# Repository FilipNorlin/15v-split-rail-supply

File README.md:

\Delta I_{L} = 0# Design and Scaling of a ±17 V 4 A DC-DC Converter with LM3478

## LM3478 Useful Design Formulas

---

### 1. Output Voltage (Boost Converter)

$$
V_{out} = V_{in} \times \frac{1}{1 - D}
$$

- $D$ = duty cycle (0 to 1)  
- $V_{in}$ = input voltage

---

### 2. Output Voltage (Inverting Buck-Boost)

$$
V_{out} = - V_{in} \times \frac{D}{1 - D}
$$

- $D$ = duty cycle  
- $V_{in}$ = input voltage

---

### 3. Inductor Selection

The inductance $L$ based on desired ripple current $\Delta I_L$:

$$
L = \frac{V_{in} \times D}{f \times \Delta I_L}
$$

- $f$ = switching frequency (Hz)  
- $\Delta I_L$ = peak-to-peak inductor ripple current (A), typically 20–40% of max load current  
- $D$ = duty cycle

---

### 4. Inductor Ripple Current

$$
\Delta I_L = \frac{V_{in} \times D}{L \times f}
$$

---

### 5. Output Capacitor Ripple Voltage

For a boost converter, output voltage ripple $\Delta V_{out}$ approximated by:

$$
\Delta V_{out} = \frac{\Delta I_L}{8 \times f \times C_{out}}
$$

- $C_{out}$ = output capacitance (F)

---

### 6. Peak Inductor Current

At max load:

$$
I_{L_{peak}} = I_{out} \times \frac{1}{1-D} + \frac{\Delta I_L}{2}
$$

---

### 7. Switch Current Limit

Current sense resistor $R_{sense}$ is:

$$
R_{sense} = \frac{V_{CS}}{I_{peak}}
$$

- $V_{CS}$ = current sense threshold voltage (typ. 156 mV)  
- $I_{peak}$ = desired max MOSFET peak current

---

### 8. Frequency Adjust Resistor Formula

To set the switching frequency $f_S$ (in Hz), use:

$$
R_{FA} = 4.503 \times 10^{11} \cdot f_S^{-1.26}
$$

Where:

- $R_{FA}$ is the resistor connected from FA/SD to ground (in ohms)
- $f_S$ is the desired switching frequency in Hz

---

### 9. Feedback Voltage Divider Formula

The output voltage is set by the resistor divider at the FB pin:

$$
V_{out} = V_{ref} \times \left(1 + \frac{R_1}{R_2}\right) = 1.26\,V \times \left(1 + \frac{R_1}{R_2}\right)
$$

- $R_1$ connected from $V_{out}$ to FB  
- $R_2$ connected from FB to ground  
- $V_{ref} = 1.26\,V$

---

## Summary Table

| Parameter                    | Formula / Value                                                      |
| ---------------------------- | -------------------------------------------------------------------- |
| Internal reference $V_{ref}$ | 1.26 V                                                               |
| Output voltage               | $V_{out} = 1.26 \times \left(1 + \frac{R_1}{R_2}\right)$             |
| Inductor value               | $L = \frac{V_{in} \times D}{f \times \Delta I_L}$                    |
| Inductor ripple current      | $\Delta I_L = \frac{V_{in} \times D}{L \times f}$                    |
| Output voltage ripple        | $\Delta V_{out} = \frac{\Delta I_L}{8 \times f \times C_{out}}$      |
| Peak inductor current        | $I_{L_{peak}} = I_{out} \times \frac{1}{1-D} + \frac{\Delta I_L}{2}$ |
| Current sense resistor       | $R_{sense} = \frac{V_{CS}}{I_{peak}}$                                |
| Switching frequency          |                                                                      |
| Max duty cycle               | $D_{max} \approx 0.85$                                               |

---

## Circuit Requirements for LM3478 ±17 V, 4 A Boost Converter And Components Scaling

The LM3478 is used to generate ±17 V rails at up to 4 A from an input voltage of **9–12 V**. LDO regulators will post-regulate the outputs to ±15 V. Components must be selected for reliability, current handling, and thermal efficiency.

---

### General Design Targets

- **Input Voltage:** 9–12 V
- **Output Voltage:** ±17 V
- **Output Current:** 4 A
- **Post-regulation:** ±15 V via LDOs
- **Switching Frequency:** 500 kHz (set using resistor on FA/SD pin)
- **Efficiency** $\approx$ $85\%$

### 1. Duty cycle

$$
D = 1 - \frac{V_{in} \cdot \eta}{V_{out}} \approx 0.52
$$
### 2. Estimate ripple current

This is a chicken and the egg problem since you need to know the ripple to get the inductor value and to need to know the inductance for the ripple. Therefore we estimate it to some percentage of the maximum output current. As mentioned before it somewhere around 20-40%.

$$
\Delta I_{L} = 0.3 \cdot I_{out(max)} \cdot \frac{V_{out}}{V_{in}}=2.27 A
$$

---

### 3. Inductance

$$
L = \frac{V_{in} \times D}{f \times \Delta I_L} = 4.4 \mu H
$$

Choose nearest standard value (e.g $4.7 \mu H$ - keep in mind typical $\pm20\%$ tolerance). A bigger Inductance will also reduce ripple. To compensate for the tolerance Im going to choose an even higher value inductor. $L=5.6 \mu H$ 

### 4. (Actual) inductor ripple current

$$
\Delta I_L = \frac{V_{in} \times D}{L \times f} = 1.77A
$$

### 5. Maximum sw./ind./diode current

$$
I_{L_{peak}} = I_{out} \times \frac{1}{1-D} + \frac{\Delta I_L}{2} = 9.77 A
$$

### 6. Estimate $C_{in}$

$$
C_{in} = \frac{I_{in} \cdot D}{f \cdot C_{in}} \approx 91 \mu F
$$

- $I_{in} \approx \frac{V_{out} \cdot I_{out}}{V_{in} \cdot \eta} = 8.9 A$

Use multiple capacitors in parallell: 
- **Fast reacting with low ESR:**
	- 2x 47 $\mu F$ (Ceramic (X7R))
- **Bulk capacitor for energy storing:**
	- 220 $\mu F$ (electrolytic/polymer)

**Input Capacitor Ripple Current:**

$$
I_{C_{in, RMS}} \approx I_{in}\cdot \sqrt{ D \cdot (1 - D) } \approx 4.42 A
$$

Input capacitors must collectively handle **~4.5 A RMS** ripple current

---

### 7. Estimate $C_{out}$

$$
C_{out} = \frac{\Delta I_{L}}{8 \cdot f \cdot \Delta V_{out}} \approx 88 \mu F
$$

To ensure **<50 mV ripple**, use at least **100 μF**.

Use multiple capacitors in parallell: 
- **Fast reacting with low ESR:**
	- 2x 47 $\mu F$ (Ceramic (X7R))
- **Bulk capacitor for energy storing:**
	- 220 $\mu F$ (electrolytic/polymer)
- ESR should be **low** (e.g., <30 mΩ)

**Output Capacitor Ripple Current:**

$$
I_{C_{out, RMS}} \approx \frac{\Delta I_{L}}{\sqrt{ 12 }} \approx 0.51 A
$$

output capacitors must collectively handle **~0.5 A RMS** ripple current

---

## Scaling and considerations

### $I_{SEN}$

The $I_{SEN}$ pin monitors the voltage across an external current-sense resistors ($R_{SEN}$). When the voltage across the resistor reaches a certain threshold the switch is turned off. This can be used to set a current limit.

$$
R_{sense} = \frac{V_{CS}}{I_{peak}}
$$
- $V_{CS} \approx 156$ mV

Lets set the maximum allowed current to 10A.

$$
R_{sense} = \frac{0.156}{10} = 15.6 \text{m} \Omega
$$
A $15$ - $20m\Omega$ can be used depending on availability and margin.

A low-inductance, high power shunt resistor (e.g 1206) is preferable. Also short clean routing is important since the ISEN pin is sensitive.

### COMP

- It is the **output of the error amplifier** inside the LM3478.
- You connect a **compensation network** (typically an **RC or RCC** network) between the **COMP pin and ground**.
- This network **sets the frequency response** of the voltage control loop.

Assuming:
- Output capacitance: $C_{out} = 100,\mu F$
- Output load: $R_{load} = \frac{V_{out}}{I_{out}} = \frac{17}{4} = 4.25,\Omega$
- Crossover frequency: $f_c \approx \frac{f_{sw}}{10} = 50,\text{kHz}$

You might choose:
- $R_c = 10,\text{k}\Omega$
- $C_c = 2.2,\text{nF}$
- (Optional) $C_f = 100,\text{pF}$

This is just a **starting guess**. Final values should be tuned via:
- **Simulation (e.g., with SPICE)**
- **Empirical testing with a Bode plot analyzer**

#### Tips
- If the output oscillates or reacts slowly, **adjust $R_c$ and $C_c$**.
- **Too much gain** → instability. **Too little gain** → sluggish response.
- Always use **short, clean traces** for the COMP network — it's a high-impedance node.

---
### FB

$$
V_{out} = V_{REF} \left(  1+ \frac{R_{1}}{R_{2}} \right)
$$
- $V_{REF} = 1.26V$

$$
\frac{R_{1}}{R_{2}} = \frac{V_{out}}{V_{REF}} - 1 \approx 12.5
$$
- $R_{2}=10k\Omega$

$$
R_{1} = 12.5 \cdot R_{2} = 125k\Omega
$$
- Close E12 value resistor is $127k\Omega$

$$
V_{out} = V_{REF} \left(  1 + \frac{R_{1}}{R_{2}} \right) = 17.26V
$$

- Use resistors ≥10 kΩ to avoid loading the output too much.
- Higher resistor values → lower quiescent power draw.
- Lower resistor values → better noise immunity.
- Avoid too high values (e.g. >500 kΩ) due to FB input bias current.

### FA/SD

$$
R_{FA} = 4.503 \cdot 10^{11} \cdot f^{-1.26} = 13.1k\Omega
$$

$R_{FA}=13k\Omega$

- Choose frequency based on trade-off:
    - **Higher f** → smaller parts, more switching loss
    - **Lower f** → bigger parts, better efficiency
- Use a **low-noise layout** for this pin — it sets timing.

---

## ✅ Component Selection Criteria

---

### 🔋 MOSFET

| Parameter                      | Specification                                             |
| ------------------------------ | --------------------------------------------------------- |
| Drain-Source Voltage $V_{DS}$  | $\geq 30\,\text{V}$ (1.5 × $V_{out}$)                     |
| Continuous Drain Current $I_D$ | $\geq 10\,\text{A}$                                       |
| On-Resistance $R_{DS(on)}$     | $\leq 20\,\text{m}\Omega$ for low conduction loss         |
| Gate Charge $Q_g$              | Low, for faster switching and less heat                   |
| Package                        | DPAK, SO-8, PowerPAK — good for hand soldering & thermals |

**Example parts:**
- IRFR3708 (30 V, 62 A, 11 mΩ, D2PAK)
- BSC026N08NS5 (80 V, 60 A, 2.6 mΩ, PowerPAK)

---

### 🌀 Inductor

| Parameter                                | Specification                          |
|------------------------------------------|----------------------------------------|
| Inductance $L$                           | $5.6\,\mu\text{H}$ (±20%)              |
| Saturation Current $I_{\text{sat}}$      | $\geq 10\text{–}12\,\text{A}$          |
| DCR (DC resistance)                      | $\leq 10\text{–}20\,\text{m}\Omega$    |
| Core Type                                | Shielded preferred (for lower EMI)     |

**Example parts:**
- Coilcraft XAL7030-562 ($5.6\,\mu\text{H}$, $15.8\,\text{A}$ $I_{\text{sat}}$, $9\,\text{m}\Omega$)
- Wurth 74437346056 ($5.6\,\mu\text{H}$, $11\,\text{A}$, $12.5\,\text{m}\Omega$)

---

### ⚡ Diode

| Parameter                                | Specification                                        |
|------------------------------------------|------------------------------------------------------|
| Reverse Voltage $V_R$                    | $\geq 30\,\text{V}$                                  |
| Average Forward Current $I_F$            | $\geq 10\,\text{A}$ avg, 20–30 A peak                |
| Type                                     | Schottky (for fast switching and low voltage drop)   |
| Package                                  | TO-220, D2PAK, PowerDI — good thermal performance    |

**Example parts:**
- STPS20L30D (30 V, 20 A, TO-220)
- SBR10U30P5 (30 V, 10 A, PowerDI 5)

---

### 🔌 Input Capacitors $C_{in}$

| Parameter                                 | Specification                                            |
|-------------------------------------------|----------------------------------------------------------|
| Capacitance $C_{in}$                      | $\geq 91\,\mu\text{F}$ total                             |
| Ripple Current Rating $I_{C_{in, RMS}}$   | $\geq 4.5\,\text{A RMS}$                                 |
| Type                                      | Mix of ceramic (low ESR) and polymer/electrolytic (bulk)|
| Configuration                             | $2 \times 47\,\mu\text{F}$ ceramic + $220\,\mu\text{F}$ bulk |

---

### 🔋 Output Capacitors $C_{out}$

| Parameter                                | Specification                                                |
| ---------------------------------------- | ------------------------------------------------------------ |
| Capacitance $C_{out}$                    | $\geq 100\,\mu\text{F}$ total                                |
| Ripple Voltage $\Delta V_{out}$          | $\leq 50\,\text{mV}$                                         |
| Ripple Current Rating $I_{C_{out, RMS}}$ | $\geq 0.5\,\text{A RMS}$                                     |
| ESR                                      | Low ESR ($\leq 30\,\text{m}\Omega$)                          |
| Type                                     | Mix of ceramic (fast) + bulk (stabilization)                 |
| Configuration                            | $2 \times 47\,\mu\text{F}$ ceramic + $220\,\mu\text{F}$ bulk |

---

## Final Design Summary

| Parameter                        | Value / Formula                                       |
|----------------------------------|-------------------------------------------------------|
| Input Voltage Range              | 9–12 V                                                |
| Output Voltage                   | ±17 V (±15 V post-regulated)                          |
| Output Current                   | 4 A                                                   |
| Efficiency (est.)                | 85%                                                   |
| Switching Frequency              | 500 kHz                                               |
| Duty Cycle (at 9 V)              | $D = 1 - \frac{V_{in} \cdot \eta}{V_{out}} \approx 0.52$ |
| Ripple Current Estimate          | $\Delta I_L = 2.27\,\text{A}$ (initial estimate)      |
| Chosen Inductor Value            | $L = 5.6\,\mu\text{H}$                                 |
| Actual Ripple Current            | $\Delta I_L = 1.77\,\text{A}$                         |
| Peak Inductor Current            | $I_{L_{peak}} = 9.77\,\text{A}$                       |
| Input Current                    | $I_{in} \approx 8.9\,\text{A}$                        |
| Input Capacitance                | $C_{in} \geq 91\,\mu\text{F}$                         |
| Input Capacitor Ripple Current   | $I_{C_{in, RMS}} \approx 4.42\,\text{A}$              |
| Output Capacitance               | $C_{out} \geq 100\,\mu\text{F}$                       |
| Output Ripple Voltage Target     | $\leq 50\,\text{mV}$                                  |
| Output Capacitor Ripple Current | $I_{C_{out, RMS}} \approx 0.51\,\text{A}$             |
| Current Sense Resistor Value     | $R_{sense} = \frac{0.156}{10} = 15.6\,\text{m}\Omega$ |
| Feedback Resistors               | $R_1 = 127\,\text{k}\Omega$, $R_2 = 10\,\text{k}\Omega$ |
| COMP Network                     | $R_c = 10\,\text{k}\Omega$, $C_c = 2.2\,\text{nF}$ (start values) |
| FA/SD Resistor                   | $R_{FA} = 13\,\text{k}\Omega$                         |

---

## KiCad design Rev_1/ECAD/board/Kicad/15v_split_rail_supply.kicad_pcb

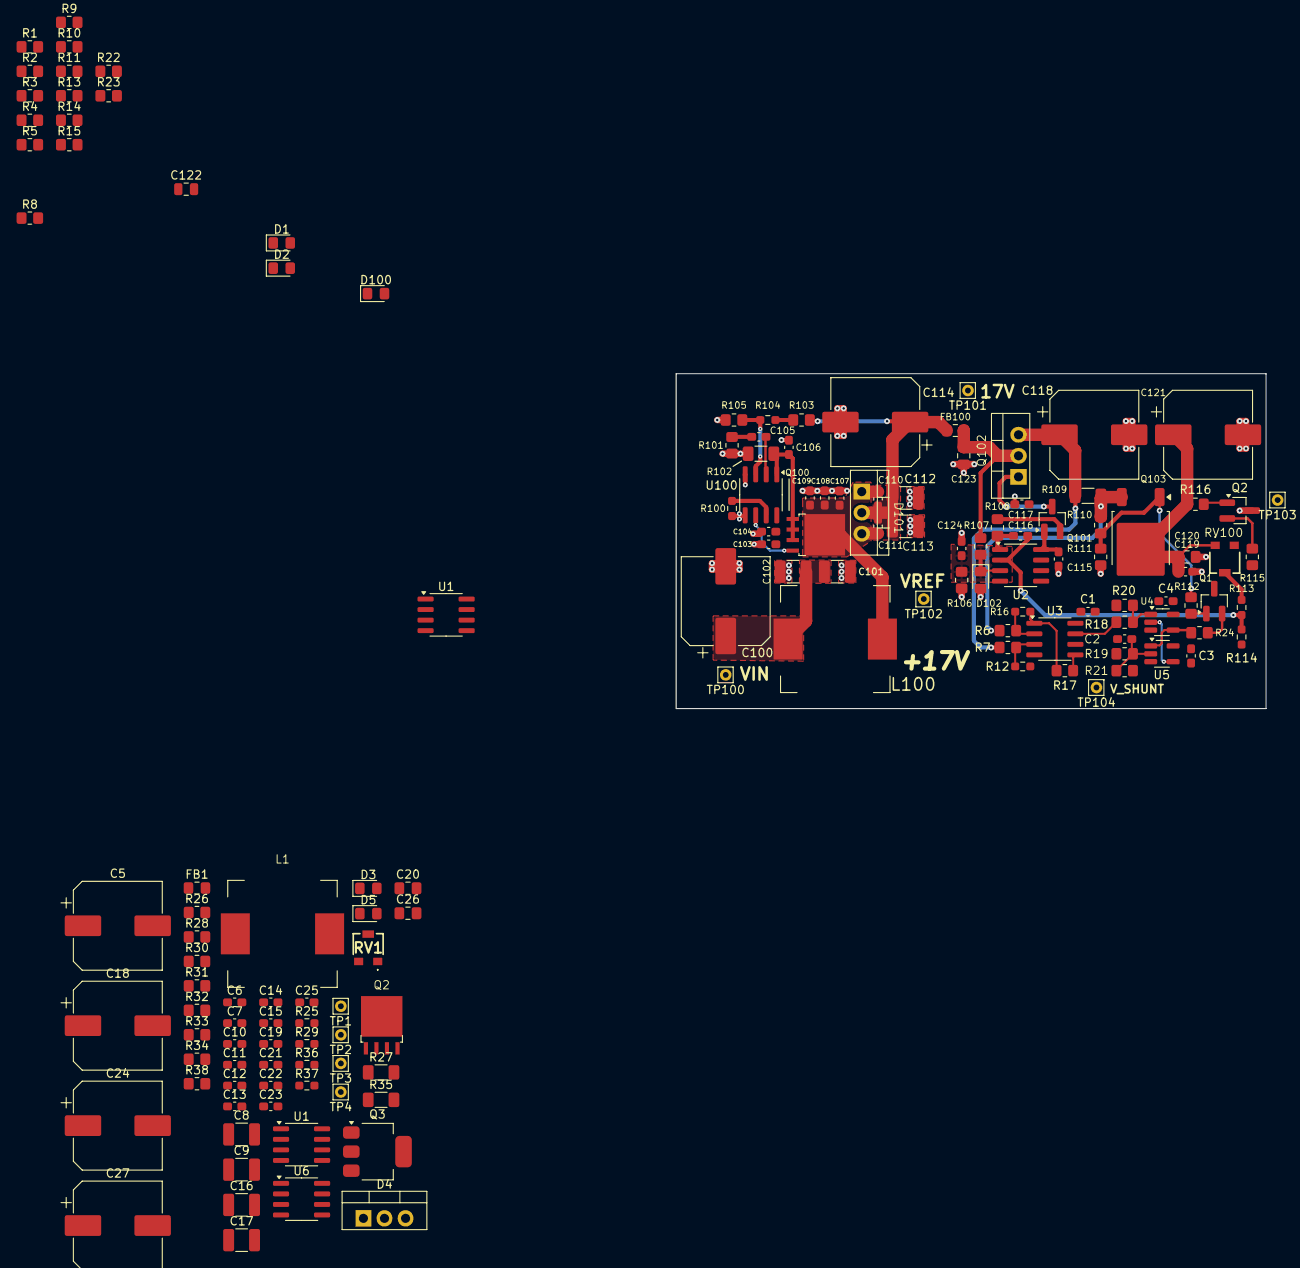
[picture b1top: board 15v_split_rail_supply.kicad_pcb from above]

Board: 4 copper layers, 71.1 x 40.4 mm, 146 parts (0 on the bottom side), 64 nets.

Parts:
C1, C2, C3, C4, C7, C11, C12, C15, C19, C21, C23, C104, C107, C108, C111, C115, C117, C124: 100n; C_0603_1608Metric_Pad1.08x0.95mm_HandSolder
C5, C18, C27, C100, C114, C121: 220u; CP_Elec_10x10.5
C6, C14, C25, C103, C109, C110, C119: 1u; C_0603_1608Metric_Pad1.08x0.95mm_HandSolder
C8, C9, C16, C17, C101, C102, C112, C113: 47u; C_1210_3225Metric_Pad1.33x2.70mm_HandSolder
C10, C105: 2.2n; C_0603_1608Metric_Pad1.08x0.95mm_HandSolder
C13, C106: 220n; C_0603_1608Metric_Pad1.08x0.95mm_HandSolder
C20, C123: 1u; C_0805_2012Metric_Pad1.18x1.45mm_HandSolder
C22, C116: 10p; C_0603_1608Metric_Pad1.08x0.95mm_HandSolder
C24, C118: 100u; CP_Elec_10x10.5
C26, C120: 10u; C_0805_2012Metric_Pad1.18x1.45mm_HandSolder
C122: 100n; C_0805_2012Metric
D1: Green; LED_0805_2012Metric_Pad1.15x1.40mm_HandSolder
D2: RED; LED_0805_2012Metric_Pad1.15x1.40mm_HandSolder
D3, D100: D_TVS; D_0805_2012Metric_Pad1.15x1.40mm_HandSolder
D4: WNS40H100CB; TO-220-3_Vertical
D5, D102: 5V6; D_0805_2012Metric_Pad1.15x1.40mm_HandSolder
D101: WNS40H100CB; TO-220-3 with HeatSink
FB1, FB100: 100; L_0805_2012Metric_Pad1.15x1.40mm_HandSolder
L1, L100: 5.6u; L_IHLP5050FD_5.0x5.0mm_Shielded
Q1, Q2#2, Q101: NPN; SOT-23_Handsoldering
Q2, Q100: IPP029N15NM6; TO-263-4_TabPin1-HandSoldered
Q3: NPN; SOT-223-3_TabPin2
Q102: NPN; TO-220-3 with HeatSink
Q103: PMOS; TO-252-2
R1, R3, R9, R14, R15, R20, R21, R26, R30, R32, R33, R101, R105, R107, R110: 10k; R_0805_2012Metric_Pad1.20x1.40mm_HandSolder
R2, R22, R23: 4k7; R_0805_2012Metric_Pad1.20x1.40mm_HandSolder
R4, R5, R6, R7, R8, R10, R11, R13, R17, R18, R19: 1k; R_0805_2012Metric_Pad1.20x1.40mm_HandSolder
R12, R16: 50k; R_0603_1608Metric_Pad0.98x0.95mm_HandSolder
R24: 1K; R_0805_2012Metric_Pad1.20x1.40mm_HandSolder
R25, R100: 13k; R_0603_1608Metric_Pad0.98x0.95mm_HandSolder
R27, R35, R102, R109: 20m; R_1206_3216Metric_Pad1.30x1.75mm_HandSolder
R28, R31, R103, R106, R111: 100k; R_0805_2012Metric_Pad1.20x1.40mm_HandSolder
R29, R104: 27k; R_0603_1608Metric_Pad0.98x0.95mm_HandSolder
R34, R108: 10; R_0805_2012Metric_Pad1.20x1.40mm_HandSolder
R36, R37, R113, R114: ?; R_0603_1608Metric_Pad0.98x0.95mm_HandSolder
R38, R112, R115, R116: 100; R_0805_2012Metric_Pad1.20x1.40mm_HandSolder
RV1, RV100: 10k; Potentiometer_SMD_Trimmer_PVG3_3.6x3
TP1, TP100, TP104: VIN; Pin_D0.7mm_L6.5mm_W1.8mm_FlatFork
TP2: -17V; Pin_D0.7mm_L6.5mm_W1.8mm_FlatFork
TP3, TP102: VREF; Pin_D0.7mm_L6.5mm_W1.8mm_FlatFork
TP4: -15V; Pin_D0.7mm_L6.5mm_W1.8mm_FlatFork
TP101: 17V; Pin_D0.7mm_L6.5mm_W1.8mm_FlatFork
TP103: 15V; Pin_D0.7mm_L6.5mm_W1.8mm_FlatFork
U1, U1#2, U100: LM3478MA; SOIC-8_3.9x4.9mm_P1.27mm
U2, U3, U6: LM358; SOIC-8_3.9x4.9mm_P1.27mm
U4, U5: SN74AHC1G02DBVR; SOT-23-5_HandSoldering

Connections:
+5V: C1.2, C2.1, C3.1, C4.1, R1.1, U3.8 (V+), U4.5 (VCC), U5.5 (VCC)
+15V: C119.1, C120.1, C121.1, C122.1, Q103.2 (D), R116.2, RV100.1, TP103.1
+17V: C115.2, C123.1, FB100.2, Q101.1 (C), Q102.2 (C), R107.1, U2.8 (V+)
-15V: C25.1, C26.1, C27.1, R35.2, RV1.1, TP4.1
-17V: C20.1, C21.1, FB1.2, Q3.3 (E), R32.1, R33.1, U6.4 (V-)
/+15V DC-DC Converter/#Q: R23.1, U4.2, U5.4
/+15V DC-DC Converter/COMP: C105.2, U100.2 (COMP)
/+15V DC-DC Converter/COMP_R2: C105.1, R101.1
/+15V DC-DC Converter/CURRENT_V_REF: R5.2, R10.2, R11.2, R13.2, R15.2, U3.6 (-)
/+15V DC-DC Converter/DIFF_NEG: R6.2, R16.2, U3.2 (-)
/+15V DC-DC Converter/DIFF_OUT: R16.1, R17.1, U3.1
/+15V DC-DC Converter/DIFF_POS: R7.2, R12.2, U3.3 (+)
/+15V DC-DC Converter/DIV: R103.2, R104.1
/+15V DC-DC Converter/DR: Q100.2 (G), U100.6 (DR)
/+15V DC-DC Converter/FA/SD: R100.1, U100.7 (FA/SD)
/+15V DC-DC Converter/FB: R104.2, R105.1, U100.3 (FB)
/+15V DC-DC Converter/ISEN: C106.1, Q100.3 (S), R102.1, U100.1 (I_{SEN})
/+15V DC-DC Converter/LOOP_OUT: C110.1, C111.1, C112.1, C113.1, C114.1, D101.2 (K), FB100.1, R103.1, TP101.1
/+15V DC-DC Converter/MOS_G: Q103.1 (G), R110.2, R111.1, R112.1
/+15V DC-DC Converter/NPN_B: Q1.2 (B), R24.2
/+15V DC-DC Converter/Q: R22.1, R24.1, U4.4, U5.1
/+15V DC-DC Converter/RESET: C2.2, R19.2, R21.1, U5.2
/+15V DC-DC Converter/SET: R18.2, R20.1, U4.1
/+15V DC-DC Converter/SET_SIG: R18.1, U3.7
/+15V DC-DC Converter/SHUNT_IN: C117.1, C118.1, Q102.3 (E), R7.1, R109.1
/+15V DC-DC Converter/SHUNT_OUT: Q103.3 (S), R6.1, R109.2, R110.1
/+15V DC-DC Converter/SHUTDOWN: Q1.1 (C), R112.2, R115.1
/+15V DC-DC Converter/SW: C107.1, C108.1, C109.1, C110.2, C111.2, D101.1 (A), D101.3 (A), L100.2, Q100.1 (D)
/+15V DC-DC Converter/V_DIFF: R17.2, TP104.1, U3.5 (+)
/+15V DC-DC Converter/V_FB: C116.2, R113.2, R114.1, U2.2 (-)
/+15V DC-DC Converter/V_IN: C100.1, C101.1, C102.1, C103.1, C104.1, D100.2 (A2), L100.1, TP100.1, U100.8 (V_{IN})
/+15V DC-DC Converter/V_REF: C124.1, D102.1 (K), R106.2, R107.2, TP102.1, U2.3 (+)
/-15V DC-DC Converter/COMP: C10.2, U1#2.2 (COMP)
/-15V DC-DC Converter/COMP_R2: C10.1, R26.1
/-15V DC-DC Converter/DIV: R28.2, R29.1
/-15V DC-DC Converter/DR: Q2.2 (G), U1#2.6 (DR)
/-15V DC-DC Converter/FA/SD: R25.1, U1#2.7 (FA/SD)
/-15V DC-DC Converter/FB: R29.2, R30.1, U1#2.3 (FB)
/-15V DC-DC Converter/ISEN: C13.1, L1.2, R27.1, U1#2.1 (I_{SEN})
/-15V DC-DC Converter/LOOP_OUT: C15.1, C16.1, C17.1, C18.1, D4.1 (A), D4.3 (A), FB1.1, R28.1, TP2.1
/-15V DC-DC Converter/SHUNT_IN: C23.1, C24.1, Q3.2 (C), R35.1
/-15V DC-DC Converter/V_FB: C22.2, R36.2, R37.1, U6.2 (-)
/-15V DC-DC Converter/V_IN: C5.1, C6.1, C7.1, C8.1, C9.1, C11.1, C12.1, C14.1, D3.2 (A2), Q2.3 (S), TP1.1, U1#2.4 (AGND), U1#2.5 (PGND)
/-15V DC-DC Converter/V_REF: C19.1, D5.2 (A), R31.2, R32.2, TP3.1, U6.3 (+)
GND: C1.1, C3.2, C4.2, C5.2, C6.2, C7.2, C8.2, C9.2, C13.2, C16.2, C17.2, C18.2, C19.2, C20.2, C25.2, C26.2, C27.2, C100.2, C101.2, C102.2, C103.2, C104.2, C106.2, C107.2, C108.2, C109.2, C112.2, C113.2, C114.2, C115.1, C117.2, C118.2, C119.2, C120.2, C121.2, C122.2, C123.2, C124.2, D1.1 (K), D2.1 (K), D3.1 (A1), D5.1 (K), D100.1 (A1), D102.2 (A), Q1.3 (E), Q2#2.3 (E), R12.1, R20.2, R21.2, R25.2, R26.2, R27.2, R30.2, R31.1, R37.2, R100.2, R101.2, R102.2, R105.2, R106.1, R111.2, R114.2, U1#2.8 (V_{IN}), U2.4 (V-), U3.4 (V-), U4.3 (GND), U5.3 (GND), U100.4 (AGND), U100.5 (PGND)
unnamed: C22.1, R34.1, U6.1
unnamed: C116.1, R108.1, U2.1
unnamed: D1.2 (A), R22.2
unnamed: D2.2 (A), R23.2
unnamed: C15.2, D4.2 (K), L1.1, Q2.1 (D)
unnamed: Q2#2.2 (B), R115.2
unnamed: Q2#2.1 (C), R116.1
unnamed: Q3.1 (B), R33.2
unnamed: Q101.2 (B), R108.2
unnamed: Q101.3 (E), Q102.1 (B)
unnamed: R2.2, R8.1
unnamed: R3.2, R9.1
unnamed: R4.2, R10.1, R11.1
unnamed: R8.2, R13.1
unnamed: R9.2, R14.1
unnamed: R14.2, R15.1
unnamed: R36.1, RV1.2
unnamed: R113.1, RV100.2
U_GND: C11.2, C12.2, C14.2, C21.2, C23.2, C24.2, U6.8 (V+)

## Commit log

2025-06-17 README update
2025-06-22 Added +17V symbol
2025-06-22 Made the schematic for +17V switch regulator
2025-06-22 Assigned footprint and 3d-models for +17V switch regulator
2025-06-28 Made the logic for Overcurrent
2025-07-09 Components for 15V regulator are placed
2025-07-12 Moved Input Capacitors to minimize loop area and created pours for boost converter
2025-07-12 Routed DC-DC Converter, needs to be looked at
2025-07-12 Routed 15V regulator
2025-07-12 Routed overcurrent logic
2025-07-31 Added inverted buck-boost for -17V rail
2025-07-31 Added U_GND symbol
2025-08-25 Added Heatsink to Transistors
2025-09-03 made sketch of cuk converter
2025-09-03 Added relative paths for the footpritns and symbol libraries
2025-09-14 -15V schematic is mostly complete
